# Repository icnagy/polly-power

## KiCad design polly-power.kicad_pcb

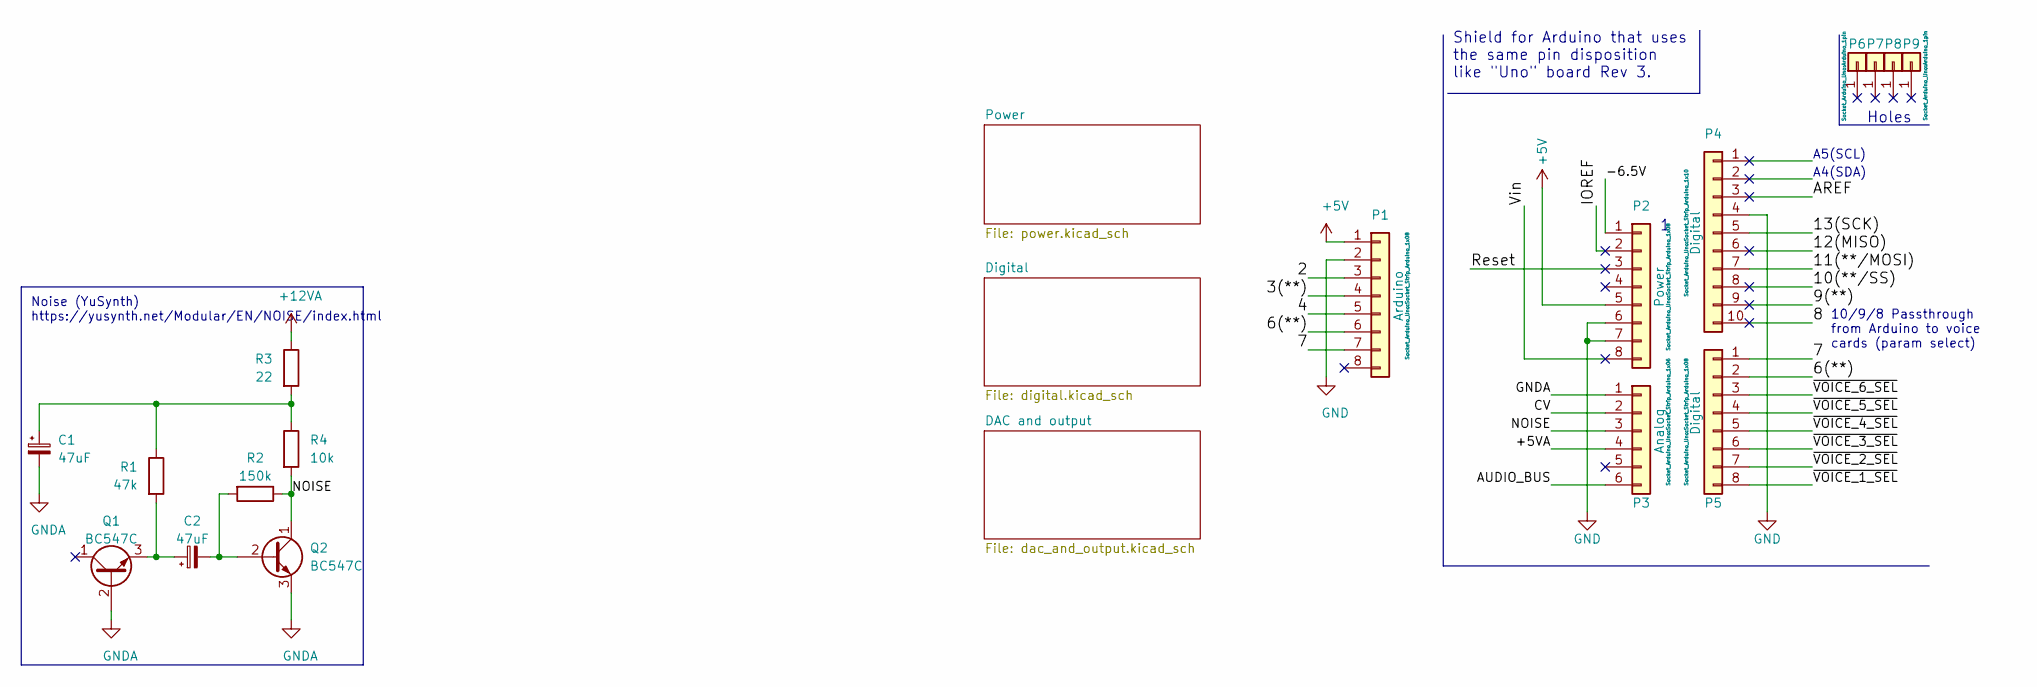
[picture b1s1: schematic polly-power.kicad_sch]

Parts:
C1, C2: 47uF; CP_Radial_D6.3mm_P2.50mm
P1: Arduino; Socket_Strip_Arduino_1x08
P2: Power; Socket_Strip_Arduino_1x08
P3: Analog; Socket_Strip_Arduino_1x06
P4: Digital; Socket_Strip_Arduino_1x10
P5: Digital; Socket_Strip_Arduino_1x08
P6, P7, P8, P9: CONN_01X01; Arduino_1pin
Q1, Q2: BC547C; TO-92_Inline
R1: 47k; R_Axial_DIN0207_L6.3mm_D2.5mm_P7.62mm_Horizontal
R2: 150k; R_Axial_DIN0207_L6.3mm_D2.5mm_P7.62mm_Horizontal
R3: 22; R_Axial_DIN0207_L6.3mm_D2.5mm_P7.62mm_Horizontal
R4: 10k; R_Axial_DIN0207_L6.3mm_D2.5mm_P7.62mm_Horizontal

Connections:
+5V: P1.1, P2.5; also elsewhere on the board
+12VA: R3.1; also elsewhere on the board
/2: P1.3
/3(**): P1.4
/4: P1.5
/6(**): P1.6, P5.2
/7: P1.7, P5.1
/8: P4.10
/9(**): P4.9
/10(**/SS): P4.8
/11(**/MOSI): P4.7
/12(MISO): P4.6
/13(SCK): P4.5
/+5VA: P3.4
/-6.5V: P2.1
/AREF: P4.3
/AUDIO_BUS: P3.6
/CV: P3.2
/IOREF: P2.2
/NOISE: P3.3, Q2.1 (C), R2.1, R4.2
/Reset: P2.3
/Vin: P2.8
/~VOICE_1_SEL: P5.8
/~VOICE_2_SEL: P5.7
/~VOICE_3_SEL: P5.6
/~VOICE_4_SEL: P5.5
/~VOICE_5_SEL: P5.4
/~VOICE_6_SEL: P5.3
GND: P1.2, P2.6, P2.7, P4.4; also elsewhere on the board
GNDA: C1.2, P3.1, Q1.2 (B), Q2.3 (E); also elsewhere on the board
unnamed: C1.1, R1.1, R3.2, R4.1
unnamed: C2.1, Q1.3 (E), R1.2
unnamed: C2.2, Q2.2 (B), R2.2

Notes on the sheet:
Noise (YuSynth) https://yusynth.net/Modular/EN/NOISE/index.html
A5(SCL)
Holes
A4(SDA)
10/9/8 Passthrough from Arduino to voice cards (param select)
Shield for Arduino that uses the same pin disposition like "Uno" board Rev 3.

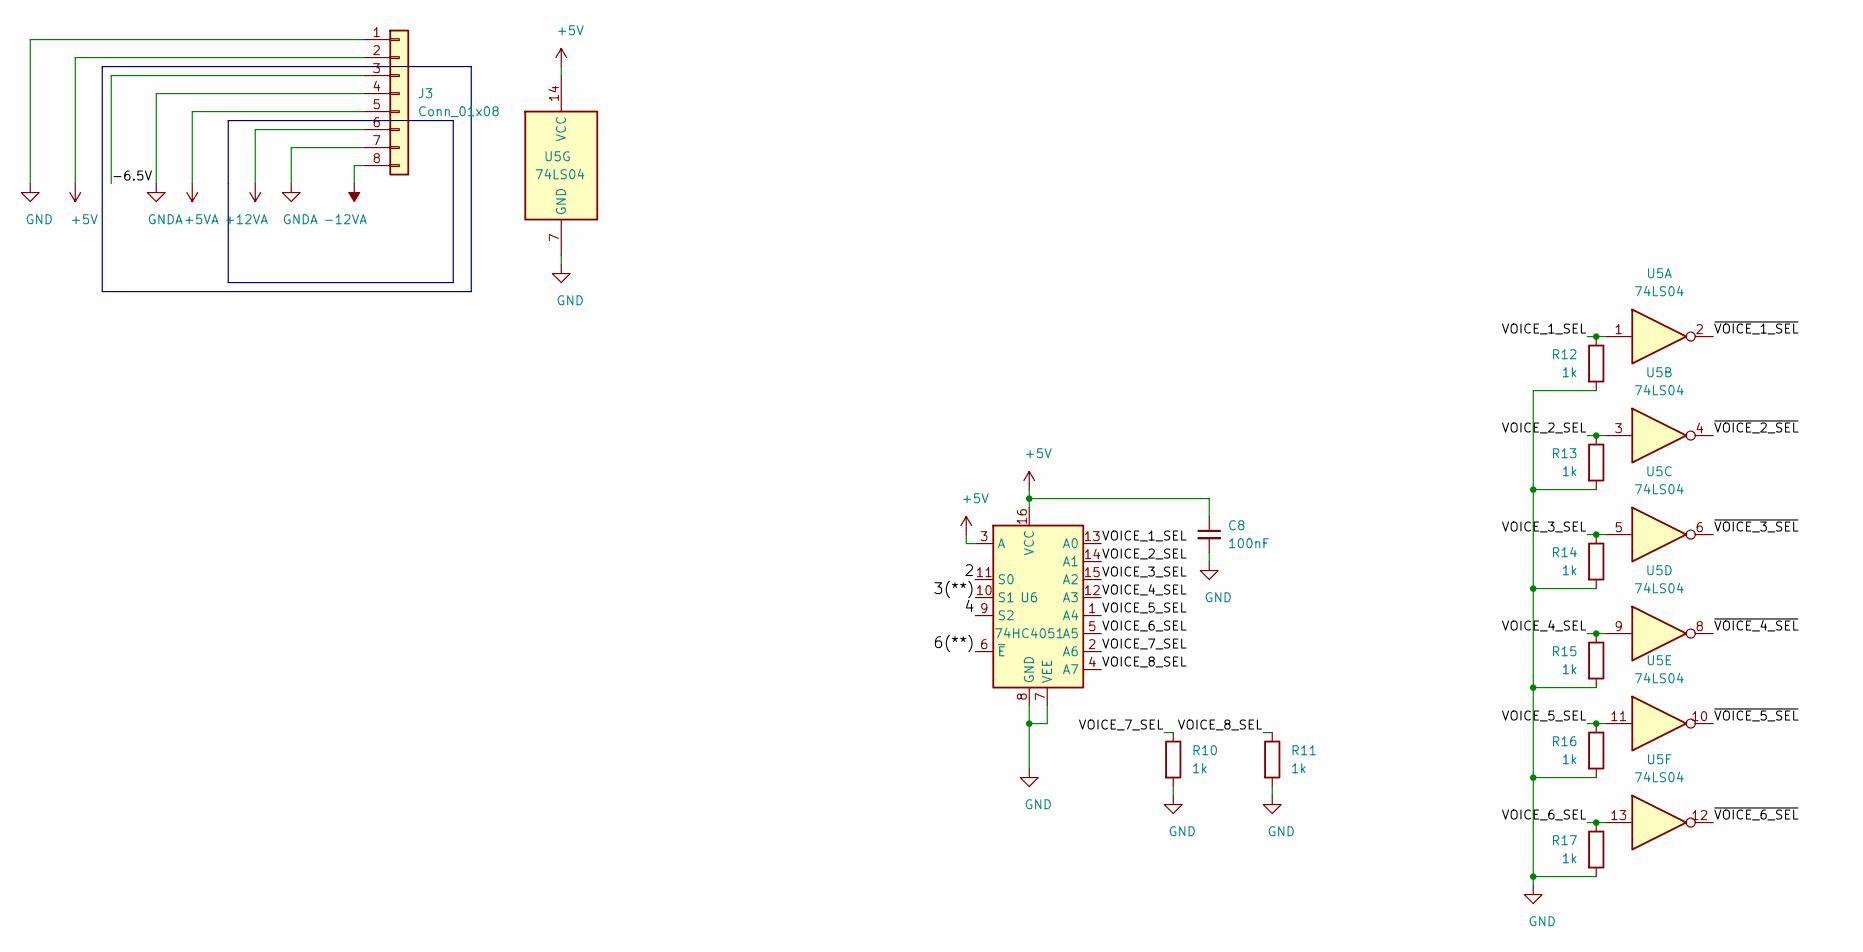
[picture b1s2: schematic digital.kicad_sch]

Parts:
C8: 100nF; C_Disc_D4.7mm_W2.5mm_P5.00mm
J3: Conn_01x08; PinHeader_1x08_P2.54mm_Vertical
R10, R11, R12, R13, R14, R15, R16, R17: 1k; R_Axial_DIN0207_L6.3mm_D2.5mm_P7.62mm_Horizontal
U5: 74LS04; DIP-14_W7.62mm_Socket_LongPads
U6: 74HC4051; DIP-16_W7.62mm_Socket_LongPads

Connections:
+5V: C8.1, J3.2, U5.14 (VCC), U6.3 (A), U6.16 (VCC); also elsewhere on the board
+5VA: J3.5; also elsewhere on the board
+12VA: J3.6; also elsewhere on the board
-12VA: J3.8; also elsewhere on the board
/Digital/2: U6.11 (S0)
/Digital/3(**): U6.10 (S1)
/Digital/4: U6.9 (S2)
/Digital/6(**): U6.6 (~E)
/Digital/-6.5V: J3.3
/Digital/VOICE_1_SEL: R12.1, U5.1, U6.13 (A0)
/Digital/VOICE_2_SEL: R13.1, U5.3, U6.14 (A1)
/Digital/VOICE_3_SEL: R14.1, U5.5, U6.15 (A2)
/Digital/VOICE_4_SEL: R15.1, U5.9, U6.12 (A3)
/Digital/VOICE_5_SEL: R16.1, U5.11, U6.1 (A4)
/Digital/VOICE_6_SEL: R17.1, U5.13, U6.5 (A5)
/Digital/VOICE_7_SEL: R10.1, U6.2 (A6)
/Digital/VOICE_8_SEL: R11.1, U6.4 (A7)
/Digital/~VOICE_1_SEL: U5.2
/Digital/~VOICE_2_SEL: U5.4
/Digital/~VOICE_3_SEL: U5.6
/Digital/~VOICE_4_SEL: U5.8
/Digital/~VOICE_5_SEL: U5.10
/Digital/~VOICE_6_SEL: U5.12
GND: C8.2, J3.1, R10.2, R11.2, R12.2, R13.2, R14.2, R15.2, R16.2, R17.2, U5.7 (GND), U6.7 (VEE), U6.8 (GND); also elsewhere on the board
GNDA: J3.4, J3.7; also elsewhere on the board

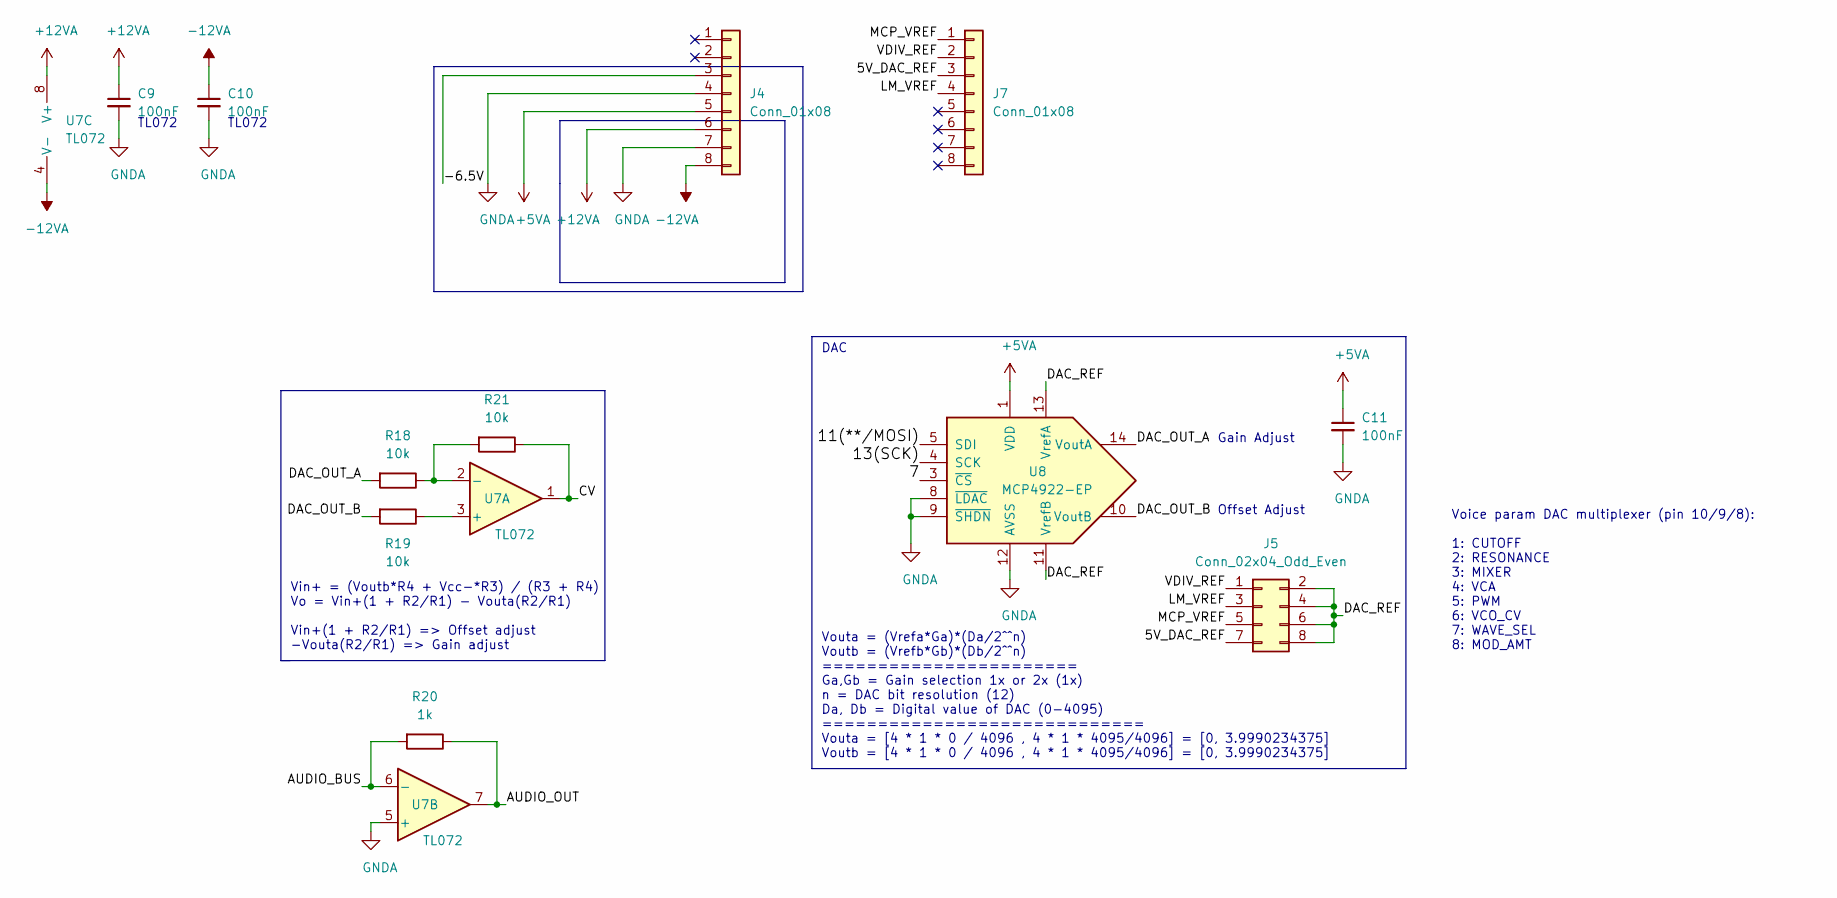
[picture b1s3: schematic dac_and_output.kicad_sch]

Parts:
C9, C10, C11: 100nF; C_Disc_D4.7mm_W2.5mm_P5.00mm
J4, J7: Conn_01x08; PinHeader_1x08_P2.54mm_Vertical
J5: Conn_02x04_Odd_Even; PinHeader_2x04_P2.54mm_Vertical
R18, R19, R21: 10k; R_Axial_DIN0207_L6.3mm_D2.5mm_P7.62mm_Horizontal
R20: 1k; R_Axial_DIN0207_L6.3mm_D2.5mm_P7.62mm_Horizontal
U7: TL072; DIP-8_W7.62mm_Socket_LongPads
U8: MCP4922-EP; DIP-14_W7.62mm_Socket_LongPads

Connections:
+5VA: C11.1, J4.5, U8.1 (VDD); also elsewhere on the board
+12VA: C9.1, J4.6, U7.8 (V+); also elsewhere on the board
-12VA: C10.1, J4.8, U7.4 (V-); also elsewhere on the board
/DAC and output/5V_DAC_REF: J5.7, J7.3
/DAC and output/7: U8.3 (~CS)
/DAC and output/11(**/MOSI): U8.5 (SDI)
/DAC and output/13(SCK): U8.4 (SCK)
/DAC and output/-6.5V: J4.3
/DAC and output/AUDIO_BUS: R20.2, U7.6 (-)
/DAC and output/AUDIO_OUT: R20.1, U7.7
/DAC and output/CV: R21.1, U7.1
/DAC and output/DAC_OUT_A: R18.2, U8.14 (VoutA)
/DAC and output/DAC_OUT_B: R19.2, U8.10 (VoutB)
/DAC and output/DAC_REF: J5.2, J5.4, J5.6, J5.8, U8.11 (VrefB), U8.13 (VrefA)
/DAC and output/LM_VREF: J5.3, J7.4
/DAC and output/MCP_VREF: J5.5, J7.1
/DAC and output/VDIV_REF: J5.1, J7.2
GNDA: C9.2, C10.2, C11.2, J4.4, J4.7, U7.5 (+), U8.8 (~LDAC), U8.9 (~SHDN), U8.12 (AVSS); also elsewhere on the board
unnamed: R18.1, R21.2, U7.2 (-)
unnamed: R19.1, U7.3 (+)

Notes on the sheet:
Vin+ = (Voutb*R4 + Vcc-*R3) / (R3 + R4) Vo = Vin+(1 + R2/R1) - Vouta(R2/R1) Vin+(1 + R2/R1) => Offset adjust -Vouta(R2/R1) => Gain adjust
Vouta = (Vrefa*Ga)*(Da/2^^n) Voutb = (Vrefb*Gb)*(Db/2^^n) ======================= Ga,Gb = Gain selection 1x or 2x (1x) n = DAC bit resolution (12) Da, Db = Digital value of DAC (0-4095) ============================= Vouta = [4 * 1 * 0 / 4096 , 4 * 1 * 4095/4096] = [0, 3.9990234375] Voutb = [4 * 1 *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
Gain Adjust
Offset Adjust
Voice param DAC multiplexer (pin 10/9/8): 1: CUTOFF 2: RESONANCE 3: MIXER 4: VCA 5: PWM 6: VCO_CV 7: WAVE_SEL 8: MOD_AMT
TL072
DAC

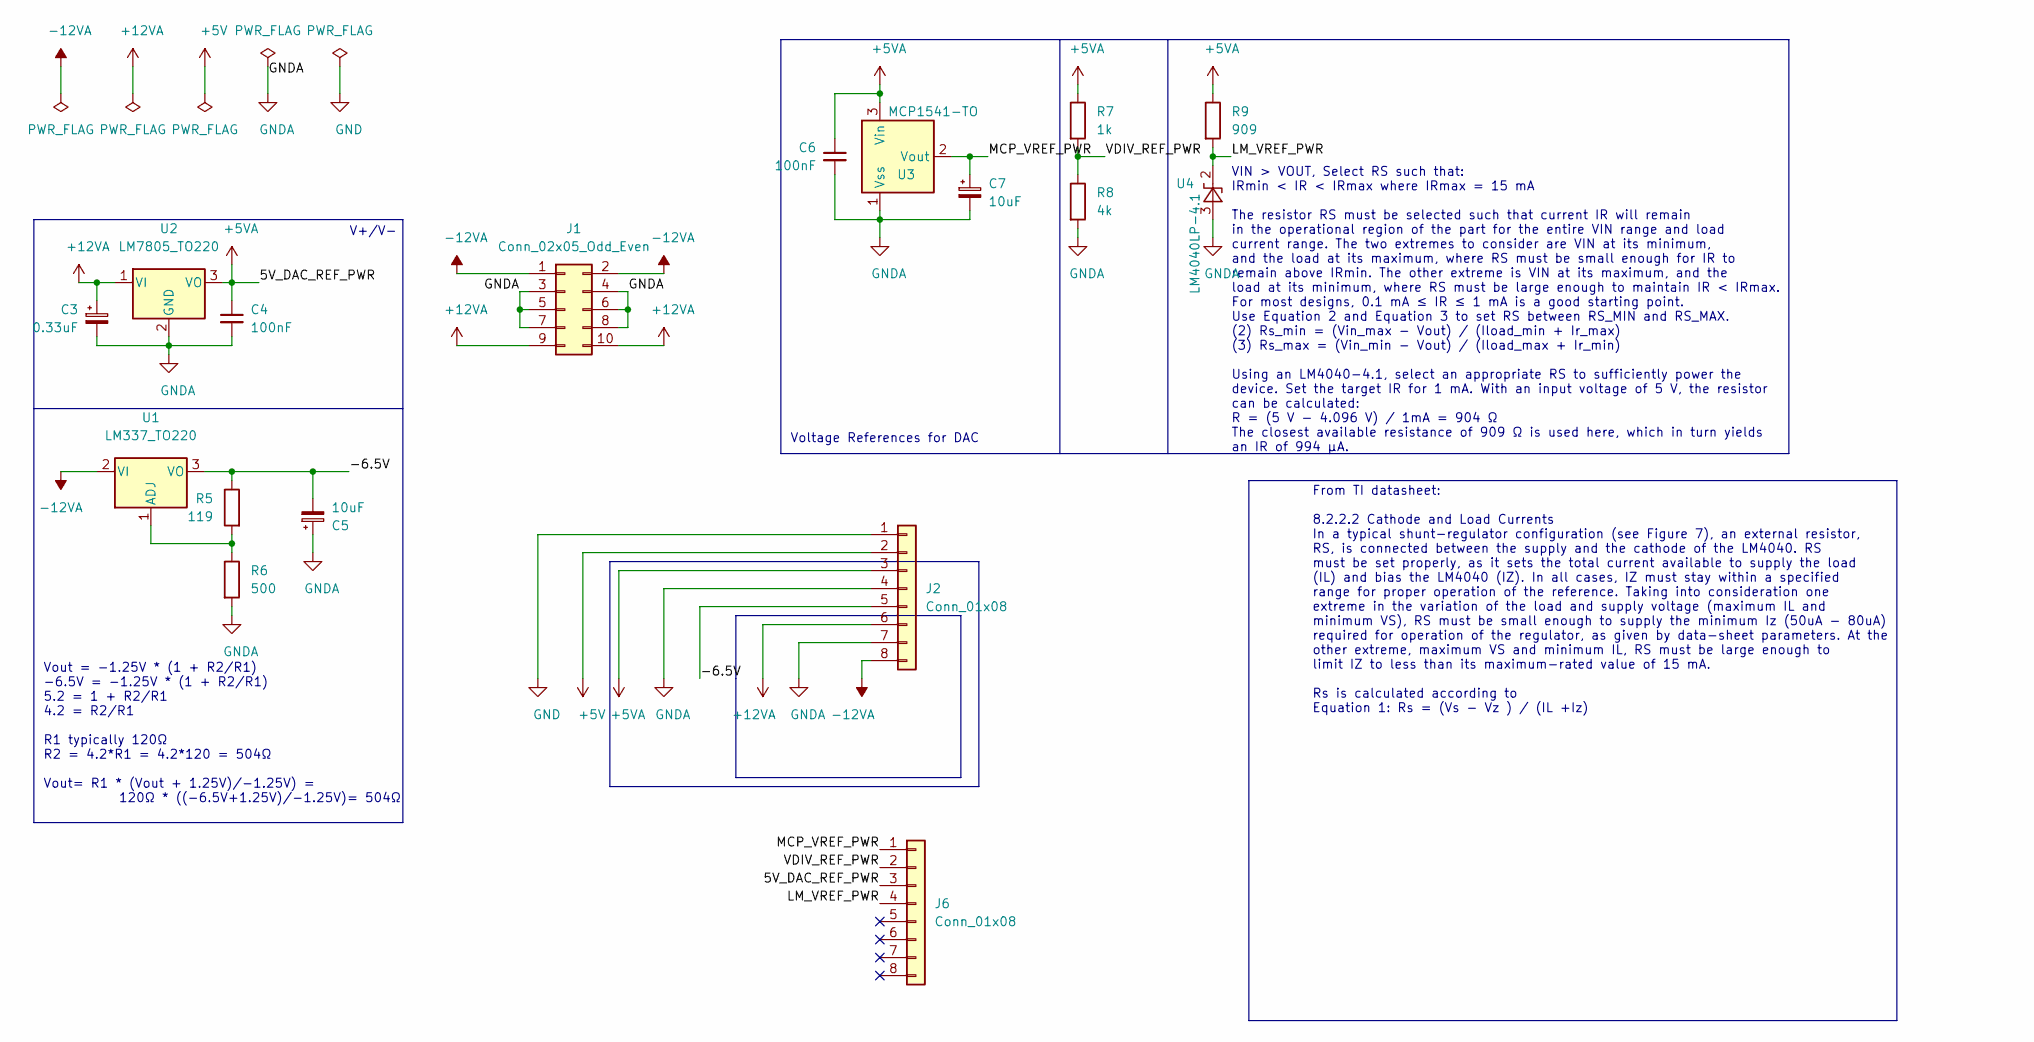
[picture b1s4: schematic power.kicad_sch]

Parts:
C3: 0.33uF; CP_Radial_D6.3mm_P2.50mm
C4, C6: 100nF; C_Disc_D4.7mm_W2.5mm_P5.00mm
C5, C7: 10uF; CP_Radial_D6.3mm_P2.50mm
J1: Conn_02x05_Odd_Even; IDC-Header_2x05_P2.54mm_Vertical
J2, J6: Conn_01x08; PinHeader_1x08_P2.54mm_Vertical
R5: 119; R_Axial_DIN0207_L6.3mm_D2.5mm_P7.62mm_Horizontal
R6: 500; R_Axial_DIN0207_L6.3mm_D2.5mm_P7.62mm_Horizontal
R7: 1k; R_Axial_DIN0207_L6.3mm_D2.5mm_P7.62mm_Horizontal
R8: 4k; R_Axial_DIN0207_L6.3mm_D2.5mm_P7.62mm_Horizontal
R9: 909; R_Axial_DIN0207_L6.3mm_D2.5mm_P7.62mm_Horizontal
U1: LM337_TO220; TO-220-3_Vertical
U2: LM7805_TO220; TO-220-3_Vertical
U3: MCP1541-TO; TO-92_Inline_Wide
U4: LM4040LP-4.1; TO-92_Inline_Wide

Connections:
+5V: J2.2; also elsewhere on the board
+5VA: C4.1, C6.1, J2.3, J6.3, R7.1, R9.1, U2.3 (VO), U3.3 (Vin); also elsewhere on the board
+12VA: C3.1, J1.9, J1.10, J2.6, U2.1 (VI); also elsewhere on the board
-12VA: J1.1, J1.2, J2.8, U1.2 (VI); also elsewhere on the board
/Power/-6.5V: C5.2, J2.5, R5.1, U1.3 (VO)
/Power/LM_VREF_PWR: J6.4, R9.2, U4.2 (K)
/Power/MCP_VREF_PWR: C7.1, J6.1, U3.2 (Vout)
/Power/VDIV_REF_PWR: J6.2, R7.2, R8.1
GND: J2.1; also elsewhere on the board
GNDA: C3.2, C4.2, C5.1, C6.2, C7.2, J1.3, J1.4, J1.5, J1.6, J1.7, J1.8, J2.4, J2.7, R6.2, R8.2, U2.2 (GND), U3.1 (Vss), U4.3 (A); also elsewhere on the board
unnamed: R5.2, R6.1, U1.1 (ADJ)

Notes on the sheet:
From TI datasheet: 8.2.2.2 Cathode and Load Currents In a typical shunt-regulator configuration (see Figure 7), an external resistor, RS, is connected between the supply and the cathode of the LM4040. RS must be set properly, as it sets the total current available to supply the load (IL) and bias t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
V+/V-
VIN > VOUT, Select RS such that: IRmin < IR < IRmax where IRmax = 15 mA The resistor RS must be selected such that current IR will remain in the operational region of the part for the entire VIN range and load current range. The two extremes to consider are VIN at its minimum, and the load at its m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
Vout = -1.25V * (1 + R2/R1) -6.5V = -1.25V * (1 + R2/R1) 5.2 = 1 + R2/R1 4.2 = R2/R1 R1 typically 120Ω R2 = 4.2*R1 = 4.2*120 = 504Ω Vout= R1 * (Vout + 1.25V)/-1.25V) = 120Ω * ((-6.5V+1.25V)/-1.25V)= 504Ω
Voltage References for DAC

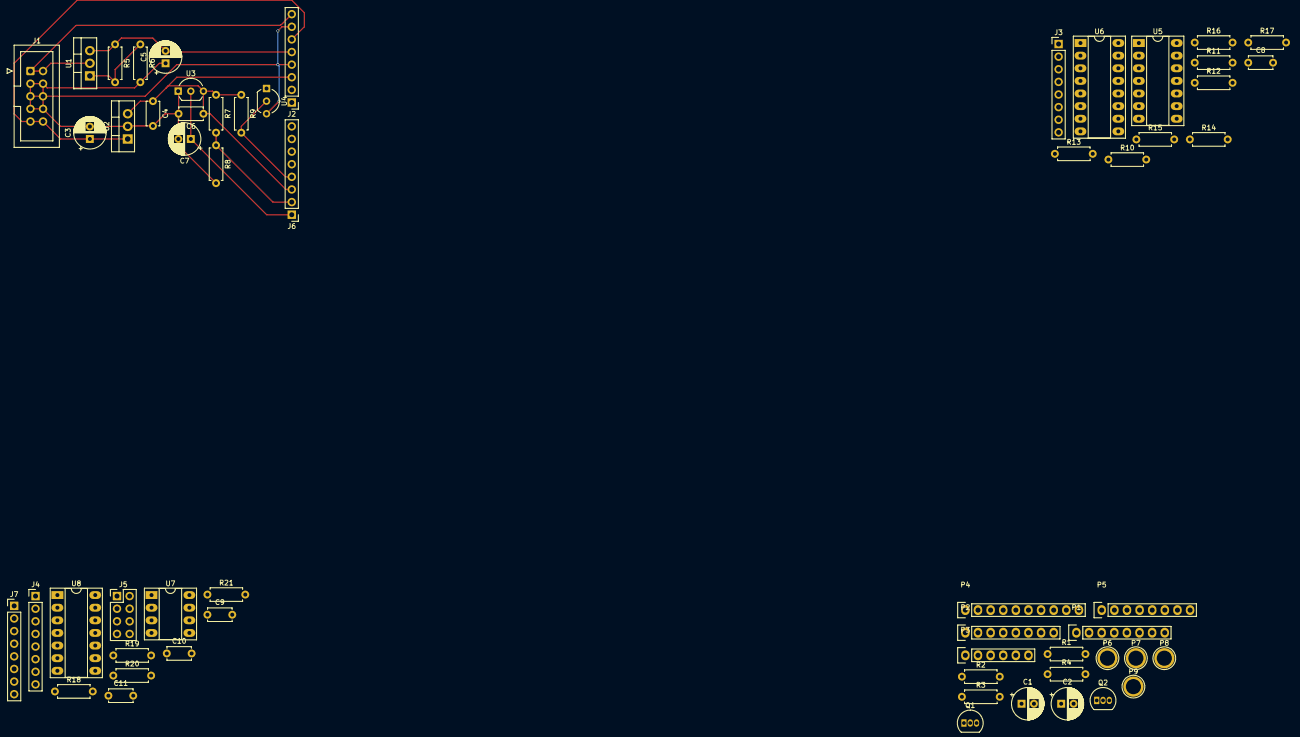
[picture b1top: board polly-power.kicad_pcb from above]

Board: 2 copper layers, 58 parts (0 on the bottom side), 37 nets.

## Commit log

2021-08-29 Tidy up
2021-09-16 Improve
2021-12-16 Continue layout
2022-01-12 Upgrade to kicad 6.0
2022-02-15 Ignore backups
2022-02-15 Tidy up after migration
2022-02-16 Split schematic into sheets
